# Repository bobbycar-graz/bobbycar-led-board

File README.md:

# bobbycar-led-board
A PCB designed for controlling lights on the bobbycar

## Features
- [ ] Control via CAN-Bus
- [ ] Webinterface
- [x] WS2812-like connector (5V-Data-GND, mr30)
- [ ] Two FET-switched DC connectors (xt30)
- [x] Current sensor to measure Power usage
- [x] VBAT voltage measurement
- [x] 5V voltage measurement (LED + Control Circuit)
- [x] SHT30 Temperature + Humidity Sensor

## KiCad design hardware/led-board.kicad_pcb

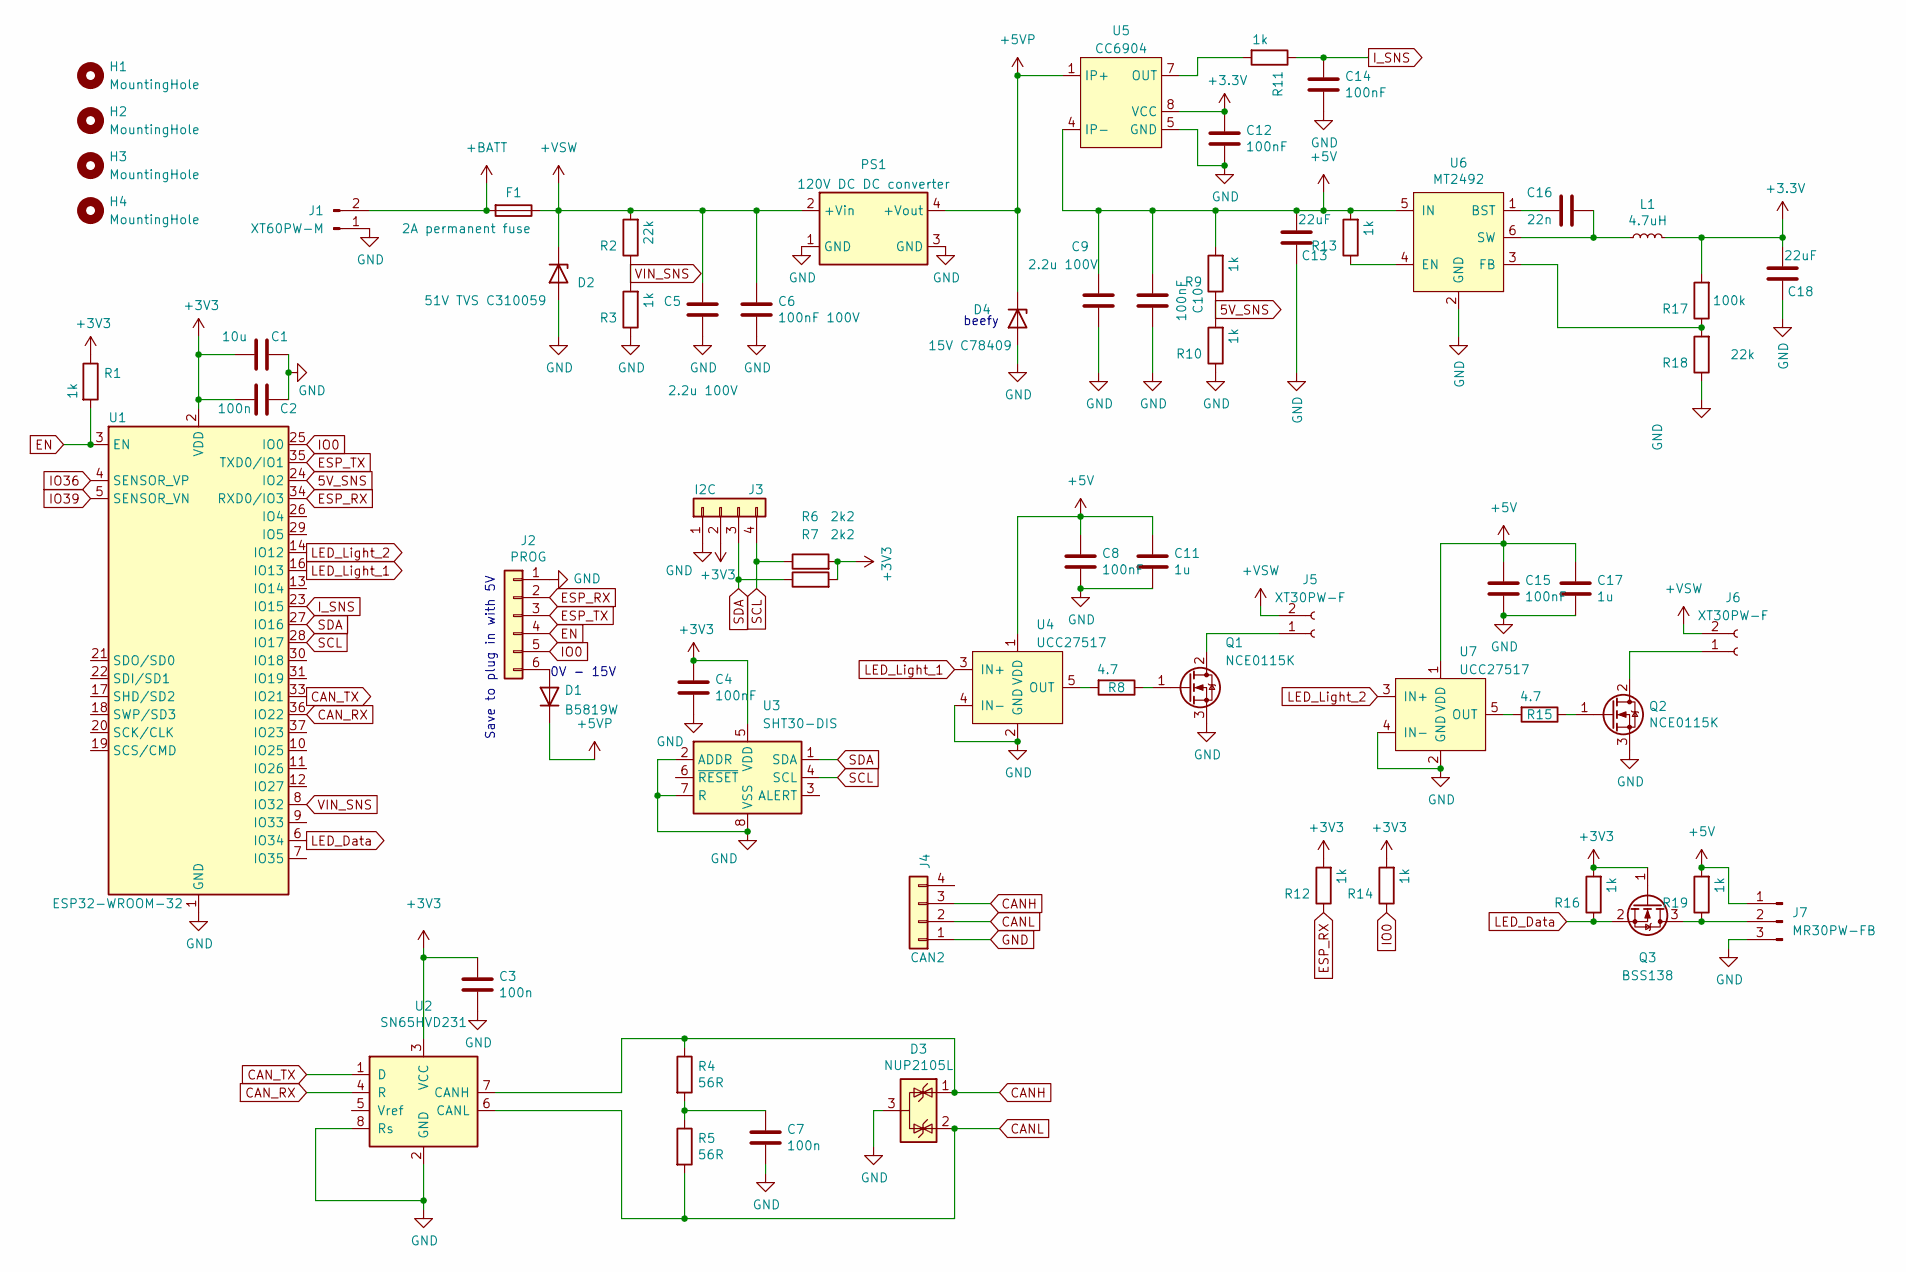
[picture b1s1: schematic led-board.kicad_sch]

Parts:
C1: 10u; C_0603_1608Metric; LCSC C19702
C2, C3, C7: 100n; C_0603_1608Metric; LCSC C14663
C4, C8, C10, C12, C14, C15: 100nF; C_0603_1608Metric; LCSC C14663
C5, C9: 2.2u 100V; C_1210_3225Metric; LCSC C76685
C6: 100nF 100V; C_0603_1608Metric; LCSC C113803
C11, C17: 1u; C_0805_2012Metric; LCSC C28323
C13, C18: 22uF; C_0805_2012Metric; LCSC C45783
C16: 22n; C_0603_1608Metric; LCSC C21122
D1: B5819W; D_SOD-123; LCSC Part # C8598
D2: 51V TVS C310059; D_SMC; LCSC C10374
D3: NUP2105L; SOT-23; LCSC C284104
D4: 15V C78409; D_SMB; LCSC C78409
F1: 2A permanent fuse; Fuse_1206_3216Metric; LCSC C182310
H1, H2, H3, H4: MountingHole; MountingHole_3.2mm_M3_DIN965_Pad
J1: XT60PW-M; Amass_XT60PW-M; LCSC C98732
J2: PROG; JST_XH_B6B-XH-A_1x06_P2.50mm_Vertical; LCSC Part # C144397
J3: I2C; JST_SH_SM04B-SRSS-TB_1x04-1MP_P1.00mm_Horizontal; LCSC C160404
J4: CAN2; JST_XH_B4B-XH-A_1x04_P2.50mm_Vertical; LCSC C144395
J5, J6: XT30PW-F; AMASS_XT30PW-F_1x02_P2.50mm_Horizontal
J7: MR30PW-FB; AMASS_MR30PW-FB_1x03_P3.50mm_Horizontal
L1: 4.7uH; L_5040; LCSC C354606
PS1: 120V DC DC converter; Converter_DCDC_120V
Q1, Q2: NCE0115K; TO-252-2; LCSC C108637
Q3: BSS138; SOT-23; LCSC C112239
R1, R3, R9, R10, R11, R12, R13, R14, R16, R19: 1k; R_0603_1608Metric; LCSC C21190
R2, R18: 22k; R_0603_1608Metric; LCSC C31850
R4, R5: 56R; R_0603_1608Metric; LCSC C25196
R6, R7: 2k2; R_0603_1608Metric; LCSC C4190
R8, R15: 4.7; R_1206_3216Metric; LCSC C17937
R17: 100k; R_0603_1608Metric; LCSC C25803
U1: ESP32-WROOM-32; LCSC C701343
U2: SN65HVD231; SOIC-8_3.9x4.9mm_P1.27mm; LCSC C30530
U3: SHT30-DIS; Sensirion_DFN-8-1EP_2.5x2.5mm_P0.5mm_EP1.1x1.7mm; LCSC C77361
U4, U7: UCC27517; SOT-23-5; LCSC C99395
U5: CC6904; SOIC-8_3.9x4.9mm_P1.27mm; LCSC C469389
U6: MT2492; SOT-23-6; LCSC C89358

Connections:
5V_SNS: R9.1, R10.2, U1.24 (IO2)
+5V: C8.1, C9.1, C10.2, C11.1, C13.2, C15.1, C17.1, J7.1, R9.2, R13.2, R19.2, U4.1 (VDD), U5.3 (IP-), U5.4 (IP-), U6.5 (IN), U7.1 (VDD)
+BATT: F1.2, J1.2
+VSW: C5.1, C6.1, D2.1 (K), F1.1, J5.2, J6.2, PS1.2 (+Vin), R2.2
CANH: D3.1 (K), J4.3, R4.1, U2.7 (CANH)
CANL: D3.2 (K), J4.2, R5.2, U2.6 (CANL)
CAN_RX: U1.36 (IO22), U2.4 (R)
CAN_TX: U1.33 (IO21), U2.1 (D)
EN: J2.4, R1.2, U1.3 (EN)
ESP_RX: J2.2, R12.1, U1.34 (RXD0/IO3)
ESP_TX: J2.3, U1.35 (TXD0/IO1)
GND: C1.1, C2.1, C3.2, C4.2, C5.2, C6.2, C7.2, C8.2, C9.2, C10.1, C11.2, C12.2, C13.1, C14.2, C15.2, C17.2, C18.1, D2.2 (A), D3.3 (A), D4.2 (A), J1.1, J2.1, J3.1, J4.1, J7.3, PS1.1 (GND), PS1.3 (GND), Q1.3 (S), Q2.3 (S), R3.1, R10.1, R18.1, U1.1 (GND), U1.15 (GND), U1.38 (GND), U1.39 (GND), U2.2 (GND), U2.8 (Rs), U3.2 (ADDR), U3.7 (R), U3.8 (VSS), U3.9 (VSS), U4.2 (GND), U4.4 (IN-), U5.5 (GND), U6.2 (GND), U7.2 (GND), U7.4 (IN-)
IO0: J2.5, R14.1, U1.25 (IO0)
IO36: U1.4 (SENSOR_VP)
IO39: U1.5 (SENSOR_VN)
I_SNS: C14.1, R11.1, U1.23 (IO15)
LED_Data: Q3.2 (S), R16.1, U1.6 (IO34)
LED_Light_1: U1.16 (IO13), U4.3 (IN+)
LED_Light_2: U1.14 (IO12), U7.3 (IN+)
unnamed: C7.1, R4.2, R5.1
unnamed: C16.1, L1.1, U6.6 (SW)
unnamed: C16.2, U6.1 (BST)
unnamed: D1.2 (A), J2.6
unnamed: J5.1, Q1.2 (D)
unnamed: J6.1, Q2.2 (D)
unnamed: J7.2, Q3.3 (D), R19.1
unnamed: Q1.1 (G), R8.1
unnamed: Q2.1 (G), R15.1
unnamed: R8.2, U4.5 (OUT)
unnamed: R11.2, U5.7 (OUT)
unnamed: R13.1, U6.4 (EN)
unnamed: R15.2, U7.5 (OUT)
unnamed: R17.1, R18.2, U6.3 (FB)
SCL: J3.4, R6.1, U1.28 (IO17), U3.4 (SCL)
SDA: J3.3, R7.1, U1.27 (IO16), U3.1 (SDA)
VIN_SNS: R2.1, R3.2, U1.8 (IO32)

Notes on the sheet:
Save to plug in with 5V
beefy
0V - 15V

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
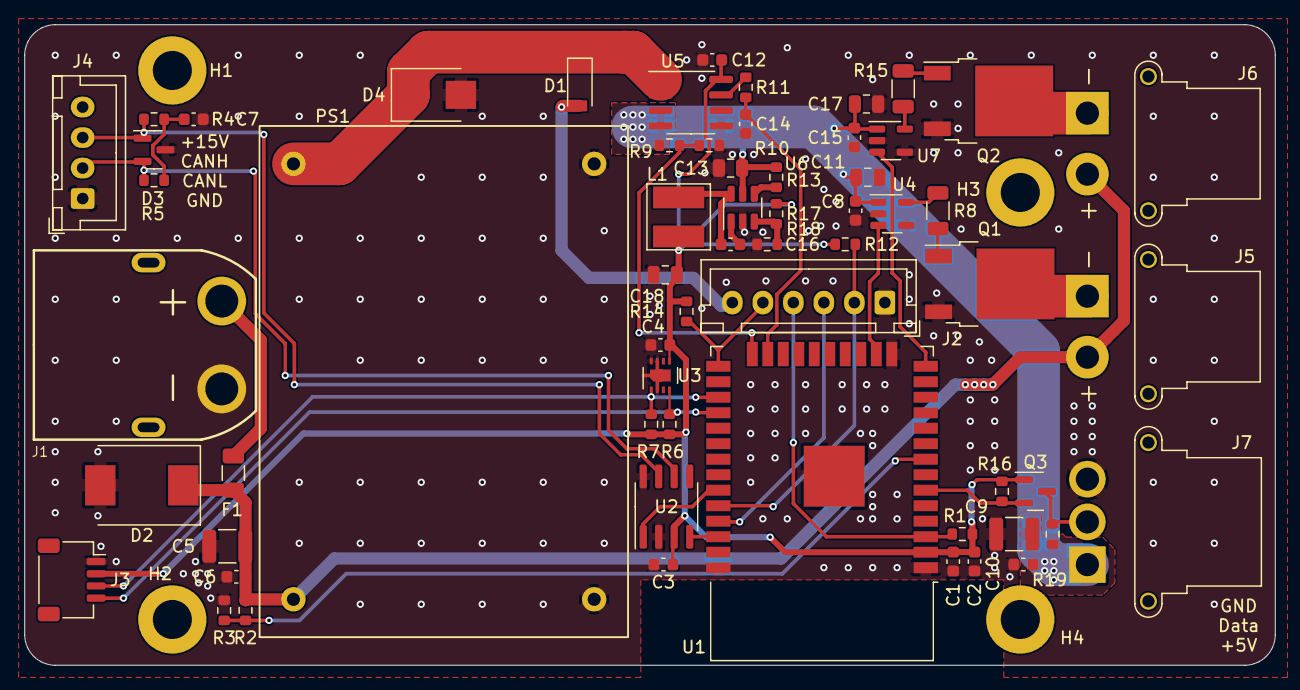
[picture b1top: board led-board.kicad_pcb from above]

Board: 2 copper layers, 102.5 x 52.5 mm, 65 parts (0 on the bottom side), 36 nets.

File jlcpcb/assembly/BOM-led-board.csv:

Comment,Designator,Footprint,LCSC
51V TVS C310059,D2,D_SMC,C10374
NCE0115K,"Q1,Q2",TO-252-2,C108637
BSS138,Q3,SOT-23,C112239
100nF 100V,C6,C_0603_1608Metric,C113803
CAN2,J4,JST_XH_B4B-XH-A_1x04_P2.50mm_Vertical,C144395
PROG,J2,JST_XH_B6B-XH-A_1x06_P2.50mm_Vertical,C144397
100nF,"C10,C12,C14,C15,C2,C3,C4,C7,C8",C_0603_1608Metric,C14663
I2C,J3,JST_SH_SM04B-SRSS-TB_1x04-1MP_P1.00mm_Horizontal,C160404
4.7,"R15,R8",R_1206_3216Metric,C17937
2A permanent fuse,F1,Fuse_1206_3216Metric,C182310
10u,C1,C_0603_1608Metric,C19702
22n,C16,C_0603_1608Metric,C21122
1k,"R1,R10,R11,R12,R13,R14,R16,R19,R3,R9",R_0603_1608Metric,C21190
56R,"R4,R5",R_0603_1608Metric,C25196
100k,R17,R_0603_1608Metric,C25803
1u,"C11,C17",C_0805_2012Metric,C28323
NUP2105L,D3,SOT-23,C284104
SN65HVD231,U2,SOIC-8_3.9x4.9mm_P1.27mm,C30530
22k,"R18,R2",R_0603_1608Metric,C31850
4.7uH,L1,L_5040,C354606
2k2,"R6,R7",R_0603_1608Metric,C4190
CC6904,U5,SOIC-8_3.9x4.9mm_P1.27mm,C469389
22uF,"C13,C18",C_0805_2012Metric,C602037
ESP32-WROOM-32,U1,ESP32-WROOM-32,C701342
2.2u 100V,"C5,C9",C_1210_3225Metric,C76685
SHT30-DIS,U3,Sensirion_DFN-8-1EP_2.5x2.5mm_P0.5mm_EP1.1x1.7mm,C77361
15V C78409,D4,D_SMB,C78409
D,D1,D_SOD-123,C8598
MT2492,U6,SOT-23-6,C89358
XT60PW-M,J1,Amass_XT60PW-M,C98732
UCC27517,"U4,U7",SOT-23-5,C99395
120V DC DC converter,PS1,Converter_DCDC_120V,
MR30PW-FB,J7,AMASS_MR30PW-FB_1x03_P3.50mm_Horizontal,
XT30PW-F,J6,AMASS_XT30PW-F_1x02_P2.50mm_Horizontal,
XT30PW-F,J5,AMASS_XT30PW-F_1x02_P2.50mm_Horizontal,
MountingHole,H2,MountingHole_3.2mm_M3_DIN965_Pad,
MountingHole,H1,MountingHole_3.2mm_M3_DIN965_Pad,
MountingHole,H4,MountingHole_3.2mm_M3_DIN965_Pad,
MountingHole,H3,MountingHole_3.2mm_M3_DIN965_Pad,

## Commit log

2022-09-20 Push of first board version
2022-09-20 update of pdf schematic
2023-06-24 Preparations for Software
2023-06-24 Added gitignore
2023-06-24 Working software
2023-06-25 Updated wrong pins
2023-06-27 Read out SHT30 sensor; preps for Ledstrip
